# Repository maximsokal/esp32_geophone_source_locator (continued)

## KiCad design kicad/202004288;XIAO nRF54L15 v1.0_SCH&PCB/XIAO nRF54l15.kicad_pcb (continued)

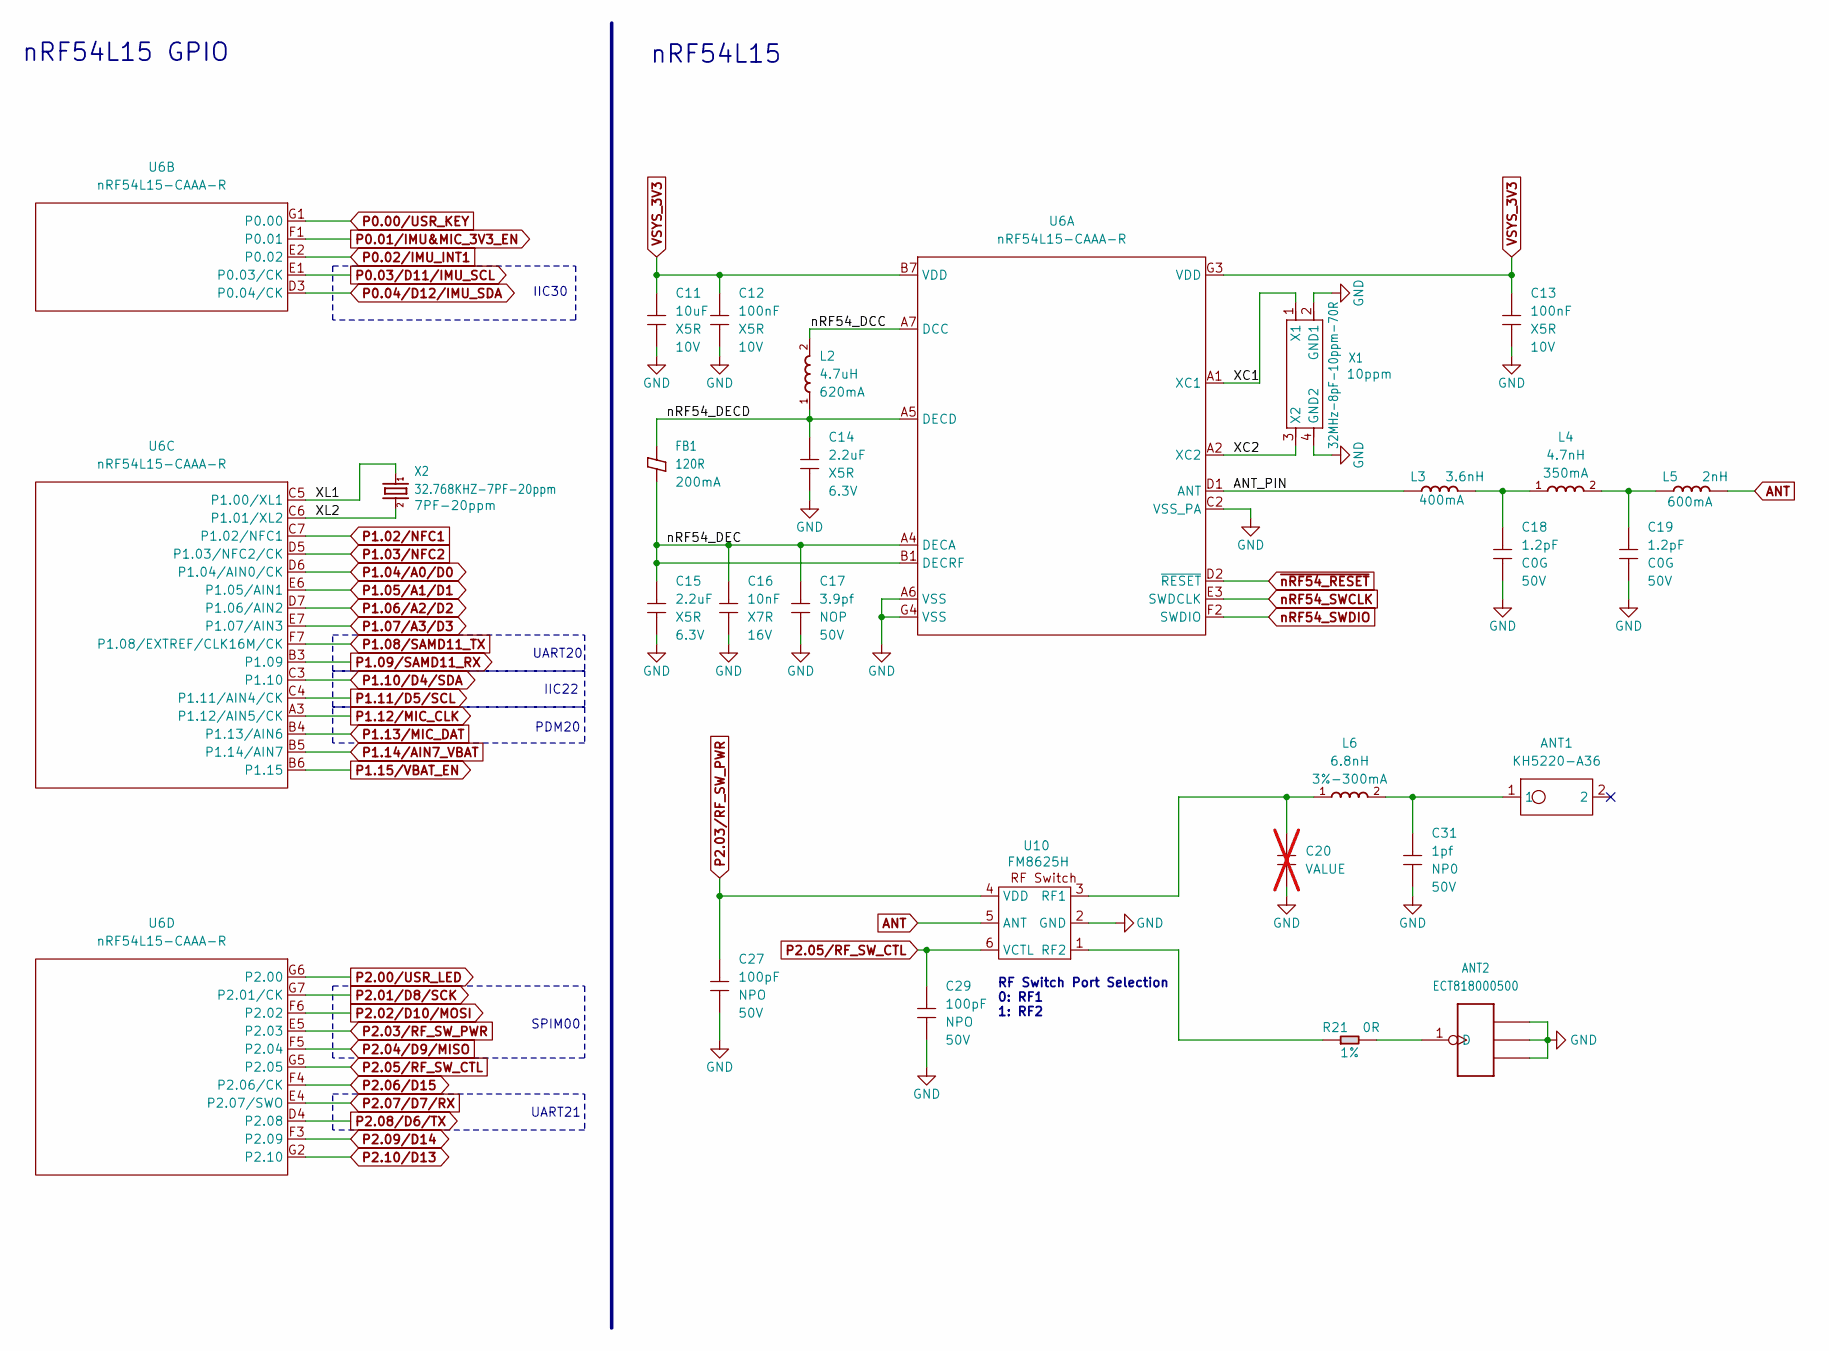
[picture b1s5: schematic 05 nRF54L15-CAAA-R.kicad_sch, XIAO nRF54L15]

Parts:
ANT1: KH5220-A36; ANT2P-5.2x2x1.1MM; MPN KH5220-A36
ANT2: ECT818000500; IPEX-GEN4-SMD-1.7X1.7X1.0MM; MPN ECT818000500
C11: 10uF; C0402; Voltage Rating 10V; MPN CC0402MRX5R6BB106
C12, C13: 100nF; C0201; Voltage Rating 10V; MPN CC0201KRX5R6BB104
C14, C15: 2.2uF; C0201; Voltage Rating 6.3V; MPN 0201X225M6R3NT
C16: 10nF; C0201; Voltage Rating 16V; MPN CC0201KRX7R7BB103
C17: 3.9pf; C0201; Voltage Rating 50V; MPN CC0201BRNPO9BN3R9
C18, C19: 1.2pF; C0201; Voltage Rating 50V; MPN GRM0335C1H1R2BA01D
C20: VALUE; C0201; not fitted
C27, C29: 100pF; C0201; Voltage Rating 50V; MPN CC0201JRNPO9BN101
C31: 1pf; C0201; Voltage Rating 50V; MPN GJM0335C1H1R0WB01D
FB1: 120R; L0201; Rating 200mA; MPN BLM03AG121SN1D
L2: 4.7uH; L0603; Rating 620mA; MPN LQM18PN4R7MFRL
L3: 3.6nH; L0201; Rating 400mA; MPN LQP03TN3N6B02D
L4: 4.7nH; L0201; Rating 350mA; MPN LQP03TN4N7J02D
L5: 2nH; L0201; Rating 600mA; MPN LQP03HQ2N0B02D
L6: 6.8nH; L0201; Rating 3%-300mA; MPN LQP03TN6N8H02D
R21: 0R; R0201; Power Rating 1%; MPN RC0201FR-070RL
U6: nRF54L15-CAAA-R; WLCSP47-0.3-2.451X2.245X0.42MM; MPN nRF54L15-CAAA-R
U10: FM8625H; DFN6-0.4-1.1X0.7X0.45MM; MPN FM8625H
X1: 32MHz-8pF-10ppm-70R; X4-SMD-1.6X1.2MM; Rating 10ppm; MPN 1S32000049
X2: 32.768KHZ-7PF-20ppm; X2-SMD-1.6X1.0MM; Rating 7PF-20ppm; MPN SC16S-7PF20PPM

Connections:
/05 nRF54L15-CAAA-R/ANT_PIN: L3.1, U6.D1 (ANT)
/05 nRF54L15-CAAA-R/XC1: U6.A1 (XC1), X1.1 (X1)
/05 nRF54L15-CAAA-R/XC2: U6.A2 (XC2), X1.3 (X2)
/05 nRF54L15-CAAA-R/XL1: U6.C5 (P1.00/XL1), X2.1
/05 nRF54L15-CAAA-R/XL2: U6.C6 (P1.01/XL2), X2.2
/05 nRF54L15-CAAA-R/nRF54_DCC: L2.2, U6.A7 (DCC)
/05 nRF54L15-CAAA-R/nRF54_DEC: C15.1, C16.1, C17.1, FB1.1, U6.A4 (DECA), U6.B1 (DECRF)
/05 nRF54L15-CAAA-R/nRF54_DECD: C14.1, FB1.2, L2.1, U6.A5 (DECD)
ANT: L5.2, U10.5 (ANT)
GND: ANT2.2 (GND1), ANT2.3 (GND1), ANT2.4 (GND2), C11.2, C12.2, C13.2, C14.2, C15.2, C16.2, C17.2, C18.2, C19.2, C20.1, C27.2, C29.2, C31.2, U6.A6 (VSS), U6.C2 (VSS_PA), U6.G4 (VSS), U10.2 (GND), X1.2 (GND1), X1.4 (GND2); also elsewhere on the board
unnamed: ANT1.1, C31.1, L6.2
unnamed: ANT2.1 (D), R21.2
unnamed: C18.1, L3.2, L4.1
unnamed: C19.1, L4.2, L5.1
unnamed: C20.2, L6.1, U10.3 (RF1)
unnamed: R21.1, U10.1 (RF2)
P0.00/USR_KEY: U6.G1 (P0.00); also elsewhere on the board
P0.01/IMU&MIC_3V3_EN: U6.F1 (P0.01); also elsewhere on the board
P0.02/IMU_INT1: U6.E2 (P0.02); also elsewhere on the board
P0.03/D11/IMU_SCL: U6.E1 (P0.03/CK); also elsewhere on the board
P0.04/D12/IMU_SDA: U6.D3 (P0.04/CK); also elsewhere on the board
P1.02/NFC1: U6.C7 (P1.02/NFC1); also elsewhere on the board
P1.03/NFC2: U6.D5 (P1.03/NFC2/CK); also elsewhere on the board
P1.04/A0/D0: U6.D6 (P1.04/AIN0/CK); also elsewhere on the board
P1.05/A1/D1: U6.E6 (P1.05/AIN1); also elsewhere on the board
P1.06/A2/D2: U6.D7 (P1.06/AIN2); also elsewhere on the board
P1.07/A3/D3: U6.E7 (P1.07/AIN3); also elsewhere on the board
P1.08/SAMD11_TX: U6.F7 (P1.08/EXTREF/CLK16M/CK); also elsewhere on the board
P1.09/SAMD11_RX: U6.B3 (P1.09); also elsewhere on the board
P1.10/D4/SDA: U6.C3 (P1.10); also elsewhere on the board
P1.11/D5/SCL: U6.C4 (P1.11/AIN4/CK); also elsewhere on the board
P1.12/MIC_CLK: U6.A3 (P1.12/AIN5/CK); also elsewhere on the board
P1.13/MIC_DAT: U6.B4 (P1.13/AIN6); also elsewhere on the board
P1.14/AIN7_VBAT: U6.B5 (P1.14/AIN7); also elsewhere on the board
P1.15/VBAT_EN: U6.B6 (P1.15); also elsewhere on the board
P2.00/USR_LED: U6.G6 (P2.00); also elsewhere on the board
P2.01/D8/SCK: U6.G7 (P2.01/CK); also elsewhere on the board
P2.02/D10/MOSI: U6.F6 (P2.02); also elsewhere on the board
P2.03/RF_SW_PWR: C27.1, U6.E5 (P2.03), U10.4 (VDD)
P2.04/D9/MISO: U6.F5 (P2.04); also elsewhere on the board
P2.05/RF_SW_CTL: C29.1, U6.G5 (P2.05), U10.6 (VCTL)
P2.06/D15: U6.F4 (P2.06/CK); also elsewhere on the board
P2.07/D7/RX: U6.E4 (P2.07/SWO); also elsewhere on the board
P2.08/D6/TX: U6.D4 (P2.08); also elsewhere on the board
P2.09/D14: U6.F3 (P2.09); also elsewhere on the board
P2.10/D13: U6.G2 (P2.10); also elsewhere on the board
VSYS_3V3: C11.1, C12.1, C13.1, U6.B7 (VDD), U6.G3 (VDD); also elsewhere on the board
nRF54_SWCLK: U6.E3 (SWDCLK); also elsewhere on the board
nRF54_SWDIO: U6.F2 (SWDIO); also elsewhere on the board
~nRF54_RESET: U6.D2 (~RESET); also elsewhere on the board

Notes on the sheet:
IIC30
nRF54L15
nRF54L15 GPIO
UART21
IIC22
RF Switch Port Selection 0: RF1 1: RF2
PDM20
SPIM00
UART20

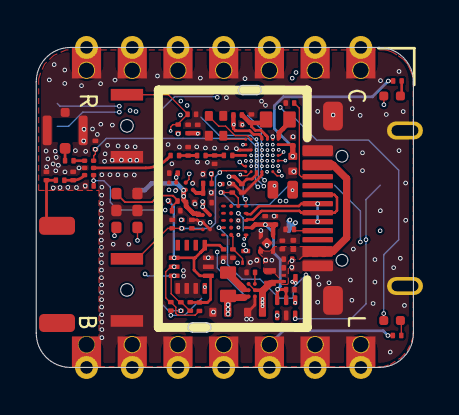
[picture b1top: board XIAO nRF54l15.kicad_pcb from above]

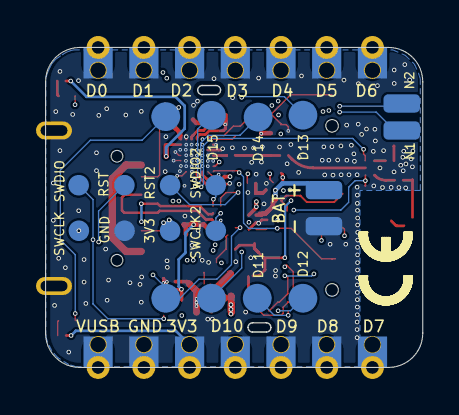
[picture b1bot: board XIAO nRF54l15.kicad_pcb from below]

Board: 6 copper layers, 21.0 x 17.8 mm, 101 parts (20 on the bottom side), 74 nets.
